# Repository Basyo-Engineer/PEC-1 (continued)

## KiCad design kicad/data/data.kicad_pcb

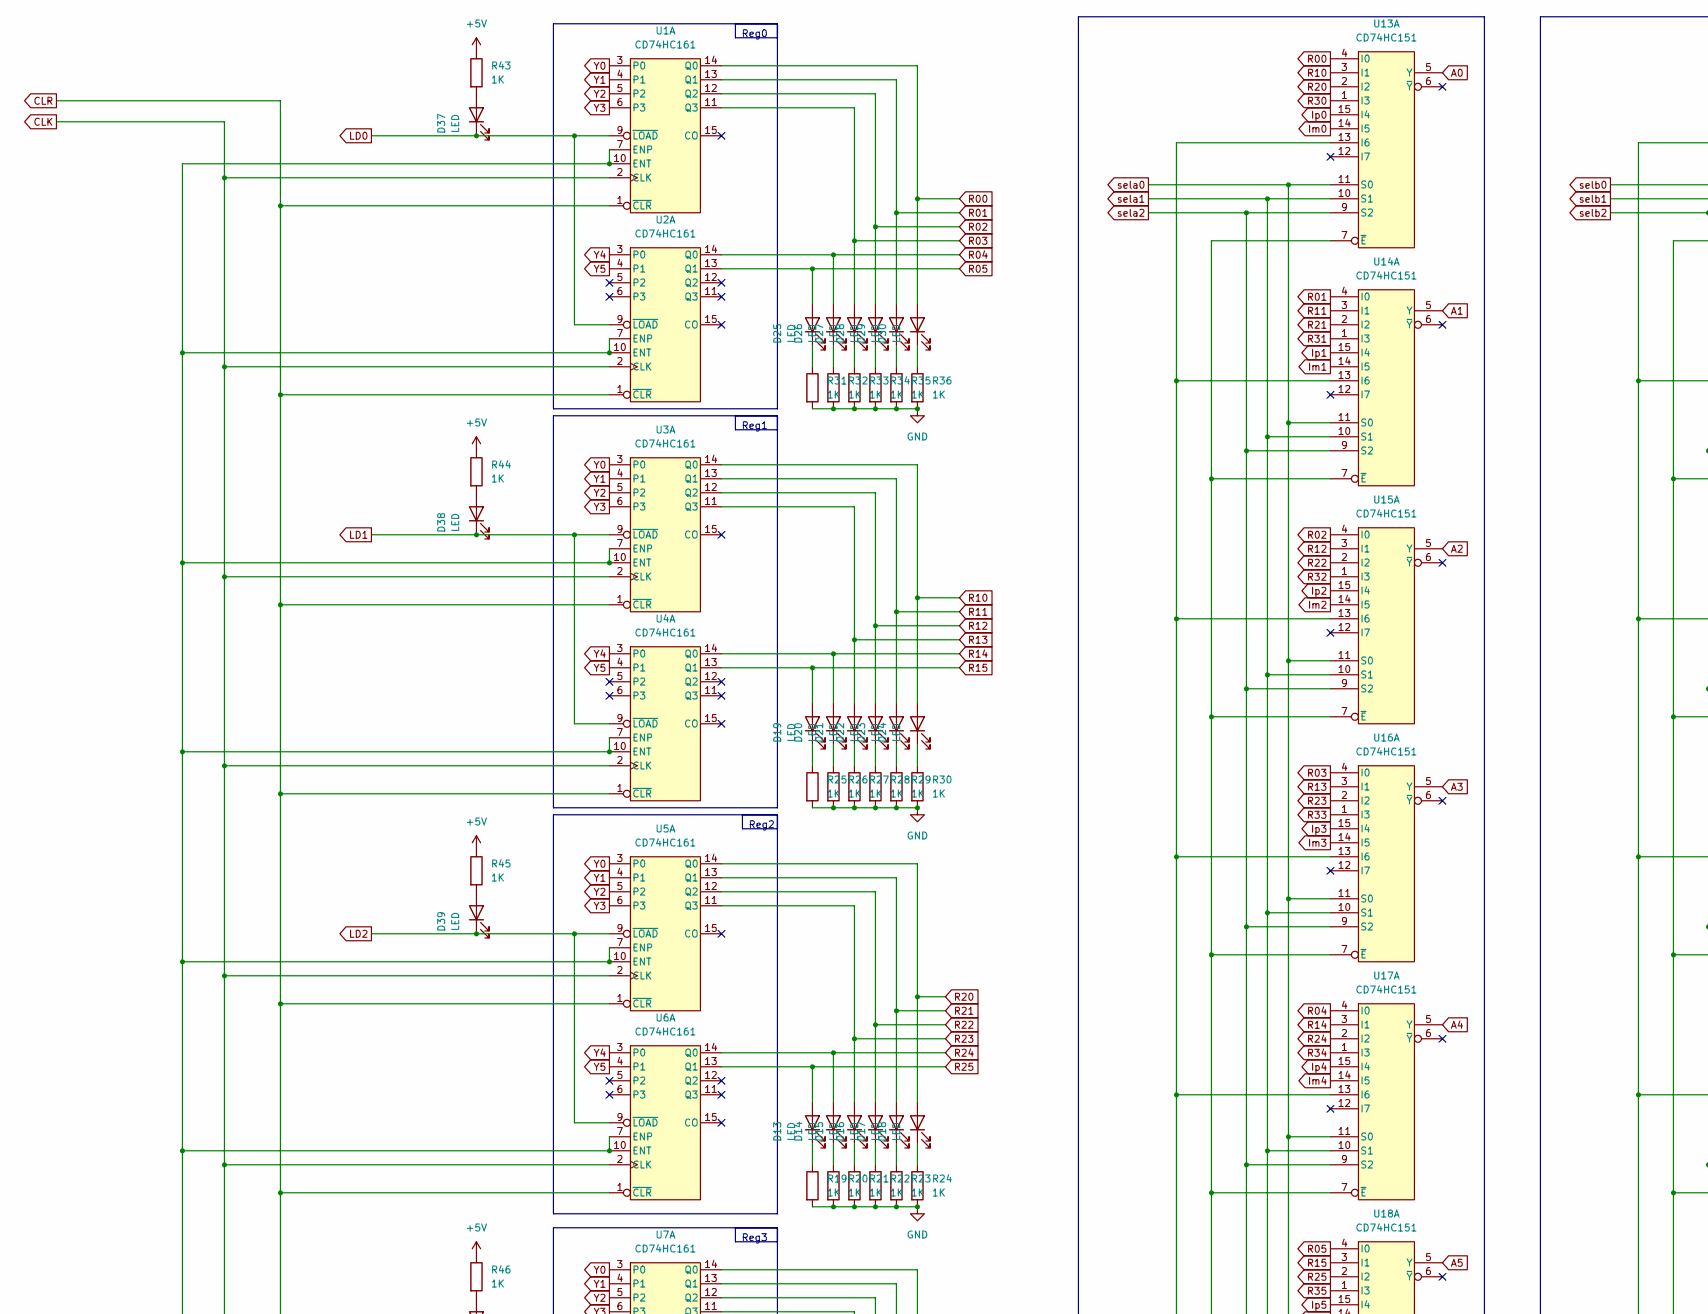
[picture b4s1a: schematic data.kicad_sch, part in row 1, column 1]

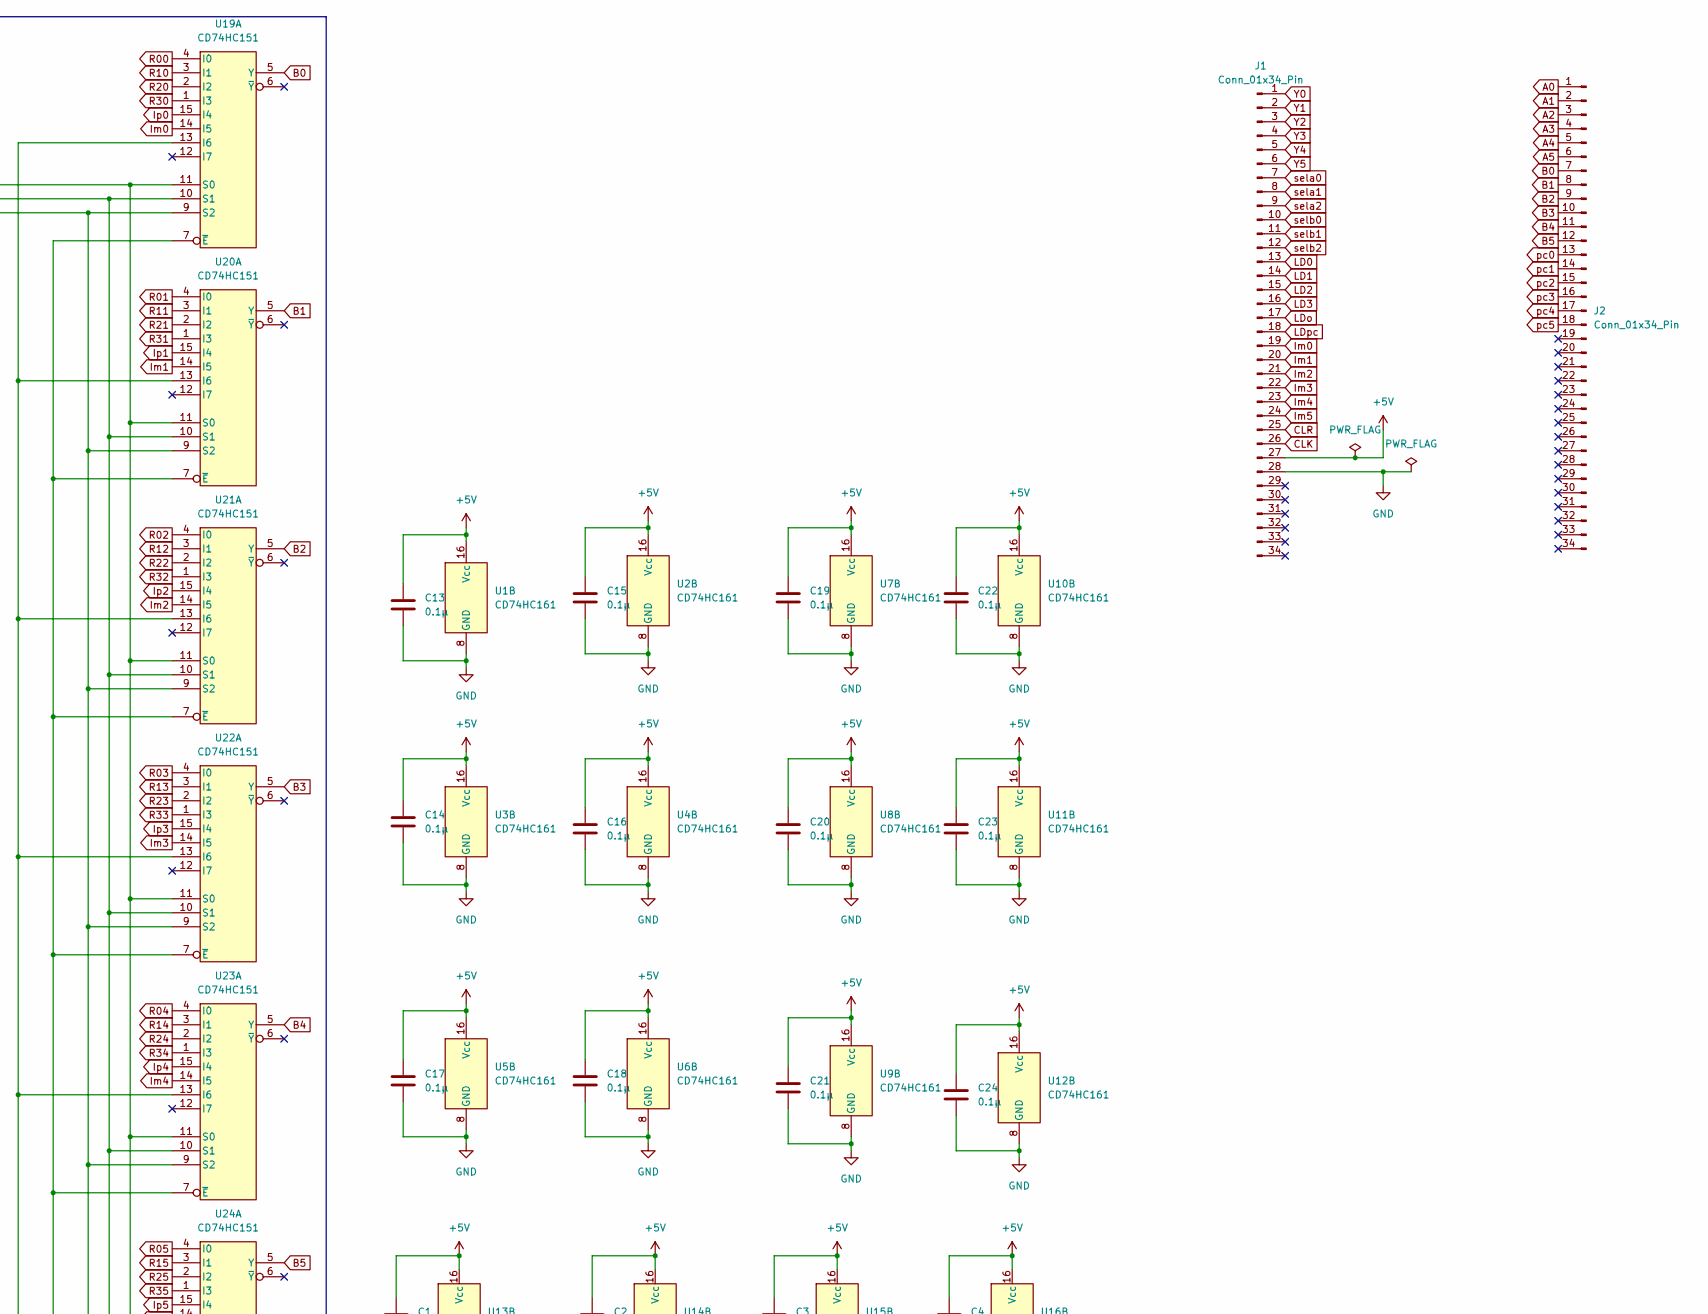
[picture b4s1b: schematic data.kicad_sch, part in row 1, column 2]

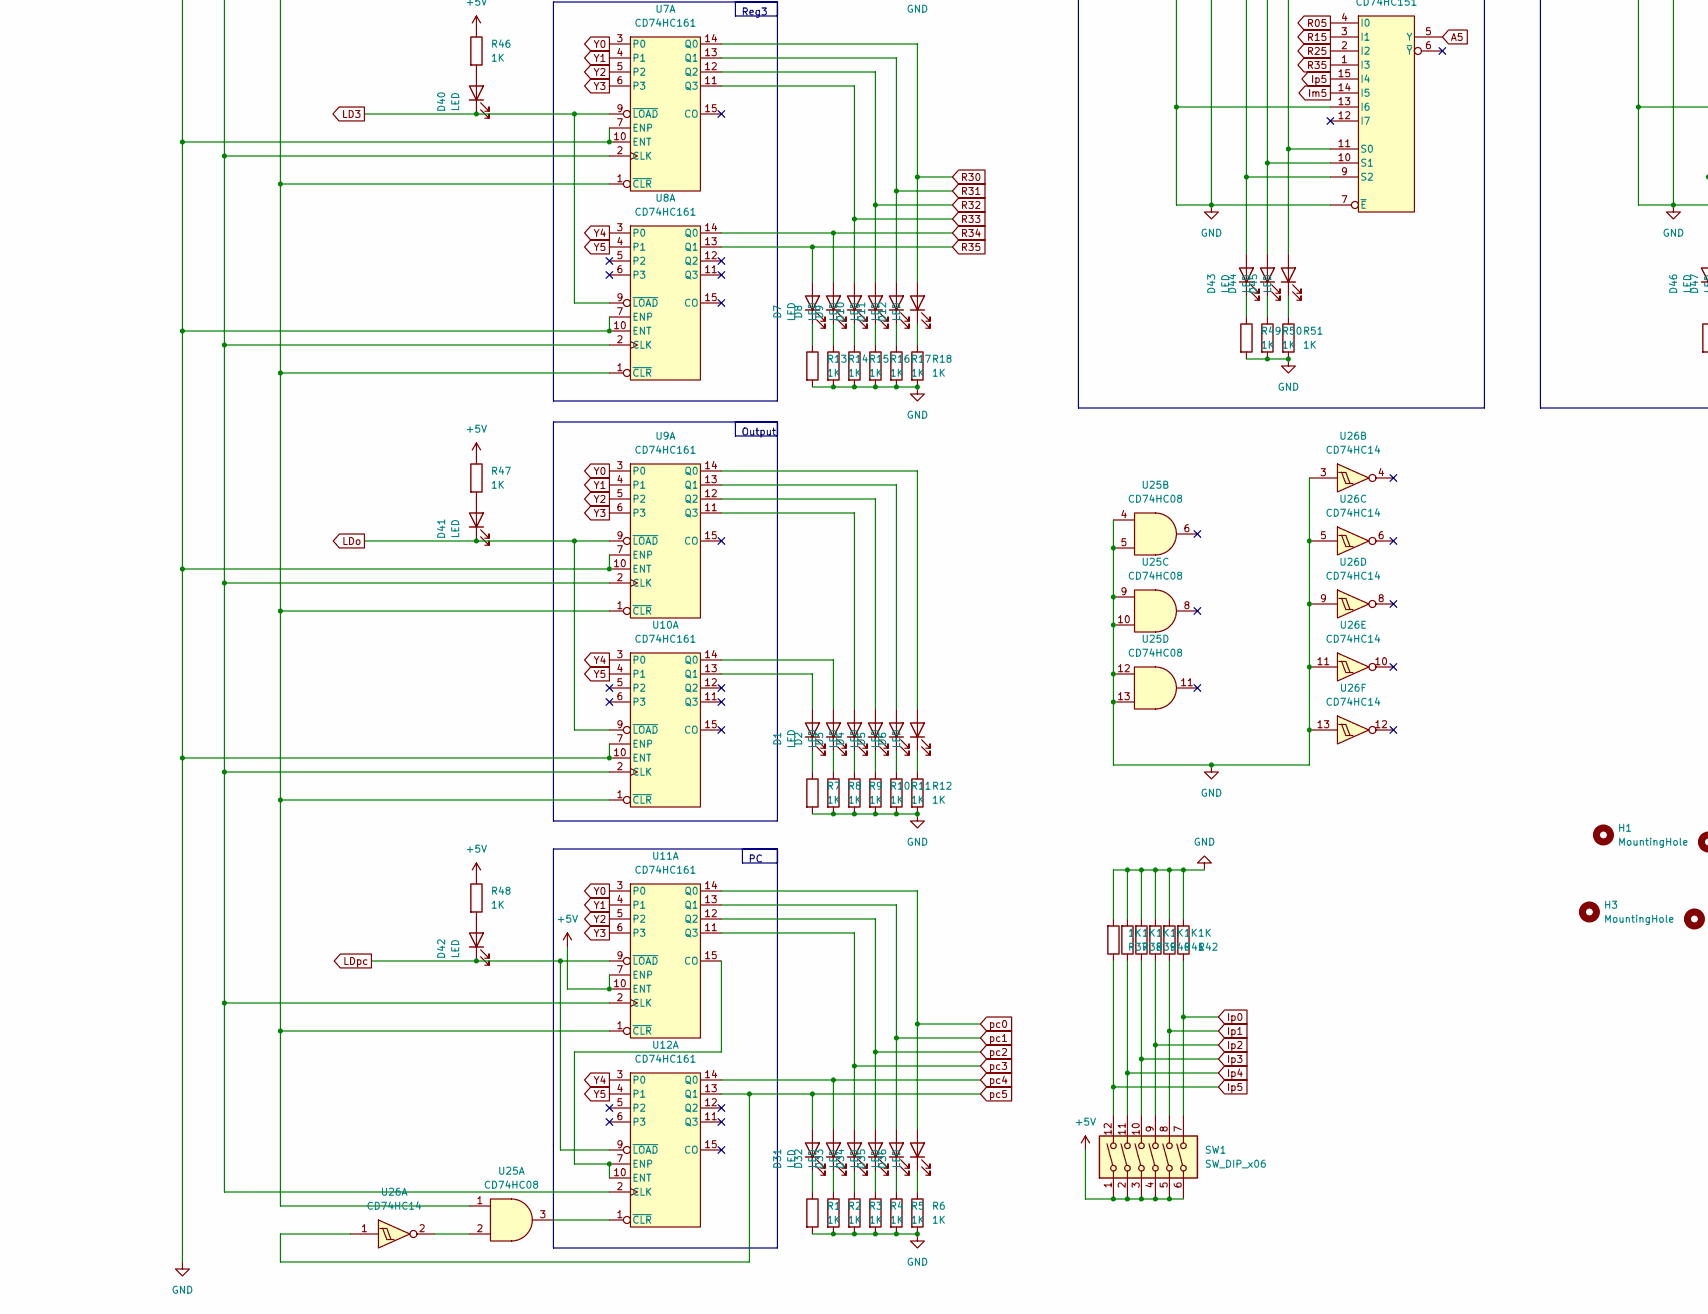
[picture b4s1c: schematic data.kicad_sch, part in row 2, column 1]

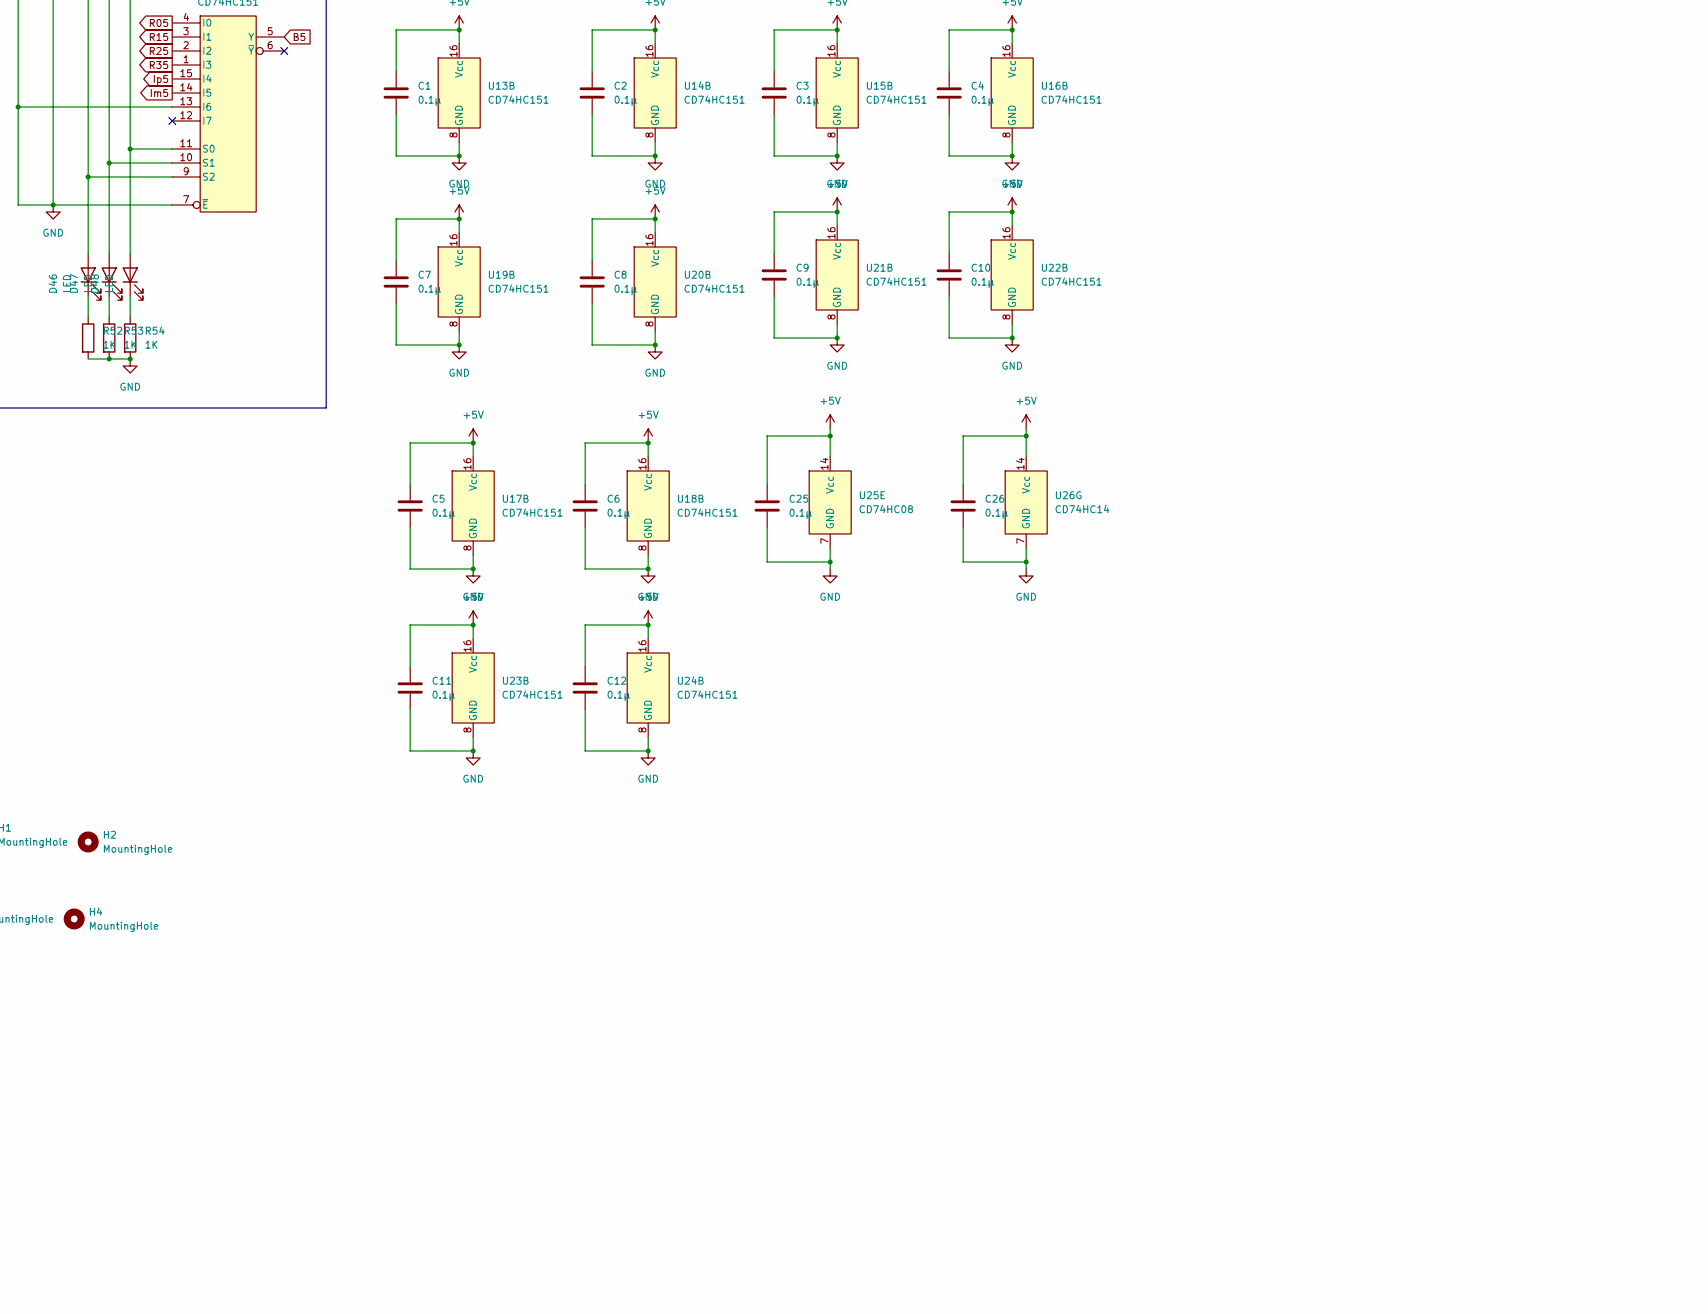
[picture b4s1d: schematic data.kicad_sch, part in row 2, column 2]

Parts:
C1, C2, C3, C4, C5, C6, C7, C8, C9, C10, C11, C12, C13, C14, C15, C16, C17, C18, C19, C20, C21, C22, C23, C24, C25, C26: 0.1μ; C_Disc_D5.0mm_W2.5mm_P2.50mm
D1, D2, D3, D4, D5, D6, D7, D8, D9, D10, D11, D12, D13, D14, D15, D16, D17, D18, D19, D20, D21, D22, D23, D24, D25, D26, D27, D28, D29, D30, D31, D32, D33, D34, D35, D36, D37, D38, D39, D40, D41, D42, D43, D44, D45, D46, D47, D48: LED; LED_D3.0mm
H1, H2, H3, H4: MountingHole; MountingHole_3.2mm_M3
J1, J2: Conn_01x34_Pin; PinHeader_2x17_P2.54mm_Horizontal
R1, R2, R3, R4, R5, R6, R7, R8, R9, R10, R11, R12, R13, R14, R15, R16, R17, R18, R19, R20, R21, R22, R23, R24, R25, R26, R27, R28, R29, R30, R31, R32, R33, R34, R35, R36, R37, R38, R39, R40, R41, R42, R43, R44, R45, R46, R47, R48, R49, R50, R51, R52, R53, R54: 1K; R_Axial_DIN0207_L6.3mm_D2.5mm_P10.16mm_Horizontal
SW1: SW_DIP_x06; DIP-12_W7.62mm_Socket
U1, U2, U3, U4, U5, U6, U7, U8, U9, U10, U11, U12: CD74HC161; DIP-16_W7.62mm_Socket
U13, U14, U15, U16, U17, U18, U19, U20, U21, U22, U23, U24: CD74HC151; DIP-16_W7.62mm_Socket
U25: CD74HC08; DIP-14_W7.62mm_Socket
U26: CD74HC14; DIP-14_W7.62mm_Socket

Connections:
+5V: C1.1, C2.1, C3.1, C4.1, C5.1, C6.1, C7.1, C8.1, C9.1, C10.1, C11.1, C12.1, C13.1, C14.1, C15.1, C16.1, C17.1, C18.1, C19.1, C20.1, C21.1, C22.1, C23.1, C24.1, C25.1, C26.1, J1.27, R43.1, R44.1, R45.1, R46.1, R47.1, R48.1, SW1.1, SW1.2, SW1.3, SW1.4, SW1.5, SW1.6, U1.16 (Vcc), U2.16 (Vcc), U3.16 (Vcc), U4.16 (Vcc), U5.16 (Vcc), U6.16 (Vcc), U7.16 (Vcc), U8.16 (Vcc), U9.16 (Vcc), U10.16 (Vcc), U11.7 (ENP), U11.10 (ENT), U11.16 (Vcc), U12.16 (Vcc), U13.16 (Vcc), U14.16 (Vcc), U15.16 (Vcc), U16.16 (Vcc), U17.16 (Vcc), U18.16 (Vcc), U19.16 (Vcc), U20.16 (Vcc), U21.16 (Vcc), U22.16 (Vcc), U23.16 (Vcc), U24.16 (Vcc), U25.14 (Vcc), U26.14 (Vcc)
A0: J2.1, U13.5 (Y)
A1: J2.2, U14.5 (Y)
A2: J2.3, U15.5 (Y)
A3: J2.4, U16.5 (Y)
A4: J2.5, U17.5 (Y)
A5: J2.6, U18.5 (Y)
B0: J2.7, U19.5 (Y)
B1: J2.8, U20.5 (Y)
B2: J2.9, U21.5 (Y)
B3: J2.10, U22.5 (Y)
B4: J2.11, U23.5 (Y)
B5: J2.12, U24.5 (Y)
CLK: J1.26, U1.2 (CLK), U2.2 (CLK), U3.2 (CLK), U4.2 (CLK), U5.2 (CLK), U6.2 (CLK), U7.2 (CLK), U8.2 (CLK), U9.2 (CLK), U10.2 (CLK), U11.2 (CLK), U12.2 (CLK)
CLR: J1.25, U1.1 (~CLR), U2.1 (~CLR), U3.1 (~CLR), U4.1 (~CLR), U5.1 (~CLR), U6.1 (~CLR), U7.1 (~CLR), U8.1 (~CLR), U9.1 (~CLR), U10.1 (~CLR), U11.1 (~CLR), U25.1
GND: C1.2, C2.2, C3.2, C4.2, C5.2, C6.2, C7.2, C8.2, C9.2, C10.2, C11.2, C12.2, C13.2, C14.2, C15.2, C16.2, C17.2, C18.2, C19.2, C20.2, C21.2, C22.2, C23.2, C24.2, C25.2, C26.2, J1.28, R1.2, R2.2, R3.2, R4.2, R5.2, R6.2, R7.2, R8.2, R9.2, R10.2, R11.2, R12.2, R13.2, R14.2, R15.2, R16.2, R17.2, R18.2, R19.2, R20.2, R21.2, R22.2, R23.2, R24.2, R25.2, R26.2, R27.2, R28.2, R29.2, R30.2, R31.2, R32.2, R33.2, R34.2, R35.2, R36.2, R37.2, R38.2, R39.2, R40.2, R41.2, R42.2, R49.2, R50.2, R51.2, R52.2, R53.2, R54.2, U1.7 (ENP), U1.8 (GND), U1.10 (ENT), U2.7 (ENP), U2.8 (GND), U2.10 (ENT), U3.7 (ENP), U3.8 (GND), U3.10 (ENT), U4.7 (ENP), U4.8 (GND), U4.10 (ENT), U5.7 (ENP), U5.8 (GND), U5.10 (ENT), U6.7 (ENP), U6.8 (GND), U6.10 (ENT), U7.7 (ENP), U7.8 (GND), U7.10 (ENT), U8.7 (ENP), U8.8 (GND), U8.10 (ENT), U9.7 (ENP), U9.8 (GND), U9.10 (ENT), U10.7 (ENP), U10.8 (GND), U10.10 (ENT), U11.8 (GND), U12.8 (GND), U13.7 (~E), U13.8 (GND), U13.13 (I6), U14.7 (~E), U14.8 (GND), U14.13 (I6), U15.7 (~E), U15.8 (GND), U15.13 (I6), U16.7 (~E), U16.8 (GND), U16.13 (I6), U17.7 (~E), U17.8 (GND), U17.13 (I6), U18.7 (~E), U18.8 (GND), U18.13 (I6), U19.7 (~E), U19.8 (GND), U19.13 (I6), U20.7 (~E), U20.8 (GND), U20.13 (I6), U21.7 (~E), U21.8 (GND), U21.13 (I6), U22.7 (~E), U22.8 (GND), U22.13 (I6), U23.7 (~E), U23.8 (GND), U23.13 (I6), U24.7 (~E), U24.8 (GND), U24.13 (I6), U25.4, U25.5, U25.7 (GND), U25.9, U25.10, U25.12, U25.13, U26.3, U26.5, U26.7 (GND), U26.9, U26.11, U26.13
Im0: J1.19, U13.14 (I5), U19.14 (I5)
Im1: J1.20, U14.14 (I5), U20.14 (I5)
Im2: J1.21, U15.14 (I5), U21.14 (I5)
Im3: J1.22, U16.14 (I5), U22.14 (I5)
Im4: J1.23, U17.14 (I5), U23.14 (I5)
Im5: J1.24, U18.14 (I5), U24.14 (I5)
Ip0: R42.1, SW1.7, U13.15 (I4), U19.15 (I4)
Ip1: R41.1, SW1.8, U14.15 (I4), U20.15 (I4)
Ip2: R40.1, SW1.9, U15.15 (I4), U21.15 (I4)
Ip3: R39.1, SW1.10, U16.15 (I4), U22.15 (I4)
Ip4: R38.1, SW1.11, U17.15 (I4), U23.15 (I4)
Ip5: R37.1, SW1.12, U18.15 (I4), U24.15 (I4)
LD0: D37.1 (K), J1.13, U1.9 (~LOAD), U2.9 (~LOAD)
LD1: D38.1 (K), J1.14, U3.9 (~LOAD), U4.9 (~LOAD)
LD2: D39.1 (K), J1.15, U5.9 (~LOAD), U6.9 (~LOAD)
LD3: D40.1 (K), J1.16, U7.9 (~LOAD), U8.9 (~LOAD)
LDo: D41.1 (K), J1.17, U9.9 (~LOAD), U10.9 (~LOAD)
LDpc: D42.1 (K), J1.18, U11.9 (~LOAD), U12.9 (~LOAD)
unnamed: D1.2 (A), U10.13 (Q1)
unnamed: D1.1 (K), R7.1
unnamed: D2.2 (A), U10.14 (Q0)
unnamed: D2.1 (K), R8.1
unnamed: D3.2 (A), U9.11 (Q3)
unnamed: D3.1 (K), R9.1
unnamed: D4.2 (A), U9.12 (Q2)
unnamed: D4.1 (K), R10.1
unnamed: D5.2 (A), U9.13 (Q1)
unnamed: D5.1 (K), R11.1
unnamed: D6.2 (A), U9.14 (Q0)
unnamed: D6.1 (K), R12.1
unnamed: D7.1 (K), R13.1
unnamed: D8.1 (K), R14.1
unnamed: D9.1 (K), R15.1
unnamed: D10.1 (K), R16.1
unnamed: D11.1 (K), R17.1
unnamed: D12.1 (K), R18.1
unnamed: D13.1 (K), R19.1
unnamed: D14.1 (K), R20.1
unnamed: D15.1 (K), R21.1
unnamed: D16.1 (K), R22.1
unnamed: D17.1 (K), R23.1
unnamed: D18.1 (K), R24.1
unnamed: D19.1 (K), R25.1
unnamed: D20.1 (K), R26.1
unnamed: D21.1 (K), R27.1
unnamed: D22.1 (K), R28.1
unnamed: D23.1 (K), R29.1
unnamed: D24.1 (K), R30.1
unnamed: D25.1 (K), R31.1
unnamed: D26.1 (K), R32.1
unnamed: D27.1 (K), R33.1
unnamed: D28.1 (K), R34.1
unnamed: D29.1 (K), R35.1
unnamed: D30.1 (K), R36.1
unnamed: D31.1 (K), R1.1
unnamed: D32.1 (K), R2.1
unnamed: D33.1 (K), R3.1
unnamed: D34.1 (K), R4.1
unnamed: D35.1 (K), R5.1
unnamed: D36.1 (K), R6.1
unnamed: D37.2 (A), R43.2
unnamed: D38.2 (A), R44.2
unnamed: D39.2 (A), R45.2
unnamed: D40.2 (A), R46.2
unnamed: D41.2 (A), R47.2
unnamed: D42.2 (A), R48.2
unnamed: D43.1 (K), R49.1
unnamed: D44.1 (K), R50.1
unnamed: D45.1 (K), R51.1
unnamed: D46.1 (K), R52.1
unnamed: D47.1 (K), R53.1
unnamed: D48.1 (K), R54.1
unnamed: U11.15 (CO), U12.7 (ENP), U12.10 (ENT)
unnamed: U12.1 (~CLR), U25.3
unnamed: U25.2, U26.2
R00: D30.2 (A), U1.14 (Q0), U13.4 (I0), U19.4 (I0)
R01: D29.2 (A), U1.13 (Q1), U14.4 (I0), U20.4 (I0)
R02: D28.2 (A), U1.12 (Q2), U15.4 (I0), U21.4 (I0)
R03: D27.2 (A), U1.11 (Q3), U16.4 (I0), U22.4 (I0)
R04: D26.2 (A), U2.14 (Q0), U17.4 (I0), U23.4 (I0)
R05: D25.2 (A), U2.13 (Q1), U18.4 (I0), U24.4 (I0)
R10: D24.2 (A), U3.14 (Q0), U13.3 (I1), U19.3 (I1)
R11: D23.2 (A), U3.13 (Q1), U14.3 (I1), U20.3 (I1)
R12: D22.2 (A), U3.12 (Q2), U15.3 (I1), U21.3 (I1)
R13: D21.2 (A), U3.11 (Q3), U16.3 (I1), U22.3 (I1)
R14: D20.2 (A), U4.14 (Q0), U17.3 (I1), U23.3 (I1)
R15: D19.2 (A), U4.13 (Q1), U18.3 (I1), U24.3 (I1)
R20: D18.2 (A), U5.14 (Q0), U13.2 (I2), U19.2 (I2)
R21: D17.2 (A), U5.13 (Q1), U14.2 (I2), U20.2 (I2)
R22: D16.2 (A), U5.12 (Q2), U15.2 (I2), U21.2 (I2)
R23: D15.2 (A), U5.11 (Q3), U16.2 (I2), U22.2 (I2)
R24: D14.2 (A), U6.14 (Q0), U17.2 (I2), U23.2 (I2)
R25: D13.2 (A), U6.13 (Q1), U18.2 (I2), U24.2 (I2)
R30: D12.2 (A), U7.14 (Q0), U13.1 (I3), U19.1 (I3)
R31: D11.2 (A), U7.13 (Q1), U14.1 (I3), U20.1 (I3)
R32: D10.2 (A), U7.12 (Q2), U15.1 (I3), U21.1 (I3)
R33: D9.2 (A), U7.11 (Q3), U16.1 (I3), U22.1 (I3)
R34: D8.2 (A), U8.14 (Q0), U17.1 (I3), U23.1 (I3)
R35: D7.2 (A), U8.13 (Q1), U18.1 (I3), U24.1 (I3)
Y0: J1.1, U1.3 (P0), U3.3 (P0), U5.3 (P0), U7.3 (P0), U9.3 (P0), U11.3 (P0)
Y1: J1.2, U1.4 (P1), U3.4 (P1), U5.4 (P1), U7.4 (P1), U9.4 (P1), U11.4 (P1)
Y2: J1.3, U1.5 (P2), U3.5 (P2), U5.5 (P2), U7.5 (P2), U9.5 (P2), U11.5 (P2)
Y3: J1.4, U1.6 (P3), U3.6 (P3), U5.6 (P3), U7.6 (P3), U9.6 (P3), U11.6 (P3)
Y4: J1.5, U2.3 (P0), U4.3 (P0), U6.3 (P0), U8.3 (P0), U10.3 (P0), U12.3 (P0)
Y5: J1.6, U2.4 (P1), U4.4 (P1), U6.4 (P1), U8.4 (P1), U10.4 (P1), U12.4 (P1)
pc0: D36.2 (A), J2.13, U11.14 (Q0)
pc1: D35.2 (A), J2.14, U11.13 (Q1)
pc2: D34.2 (A), J2.15, U11.12 (Q2)
pc3: D33.2 (A), J2.16, U11.11 (Q3)
pc4: D32.2 (A), J2.17, U12.14 (Q0)
pc5: D31.2 (A), J2.18, U12.13 (Q1), U26.1
sela0: D45.2 (A), J1.7, U13.11 (S0), U14.11 (S0), U15.11 (S0), U16.11 (S0), U17.11 (S0), U18.11 (S0)
sela1: D44.2 (A), J1.8, U13.10 (S1), U14.10 (S1), U15.10 (S1), U16.10 (S1), U17.10 (S1), U18.10 (S1)
sela2: D43.2 (A), J1.9, U13.9 (S2), U14.9 (S2), U15.9 (S2), U16.9 (S2), U17.9 (S2), U18.9 (S2)
selb0: D48.2 (A), J1.10, U19.11 (S0), U20.11 (S0), U21.11 (S0), U22.11 (S0), U23.11 (S0), U24.11 (S0)
selb1: D47.2 (A), J1.11, U19.10 (S1), U20.10 (S1), U21.10 (S1), U22.10 (S1), U23.10 (S1), U24.10 (S1)
selb2: D46.2 (A), J1.12, U19.9 (S2), U20.9 (S2), U21.9 (S2), U22.9 (S2), U23.9 (S2), U24.9 (S2)

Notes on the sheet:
Reg3
Reg0
Reg1
Output
Reg2

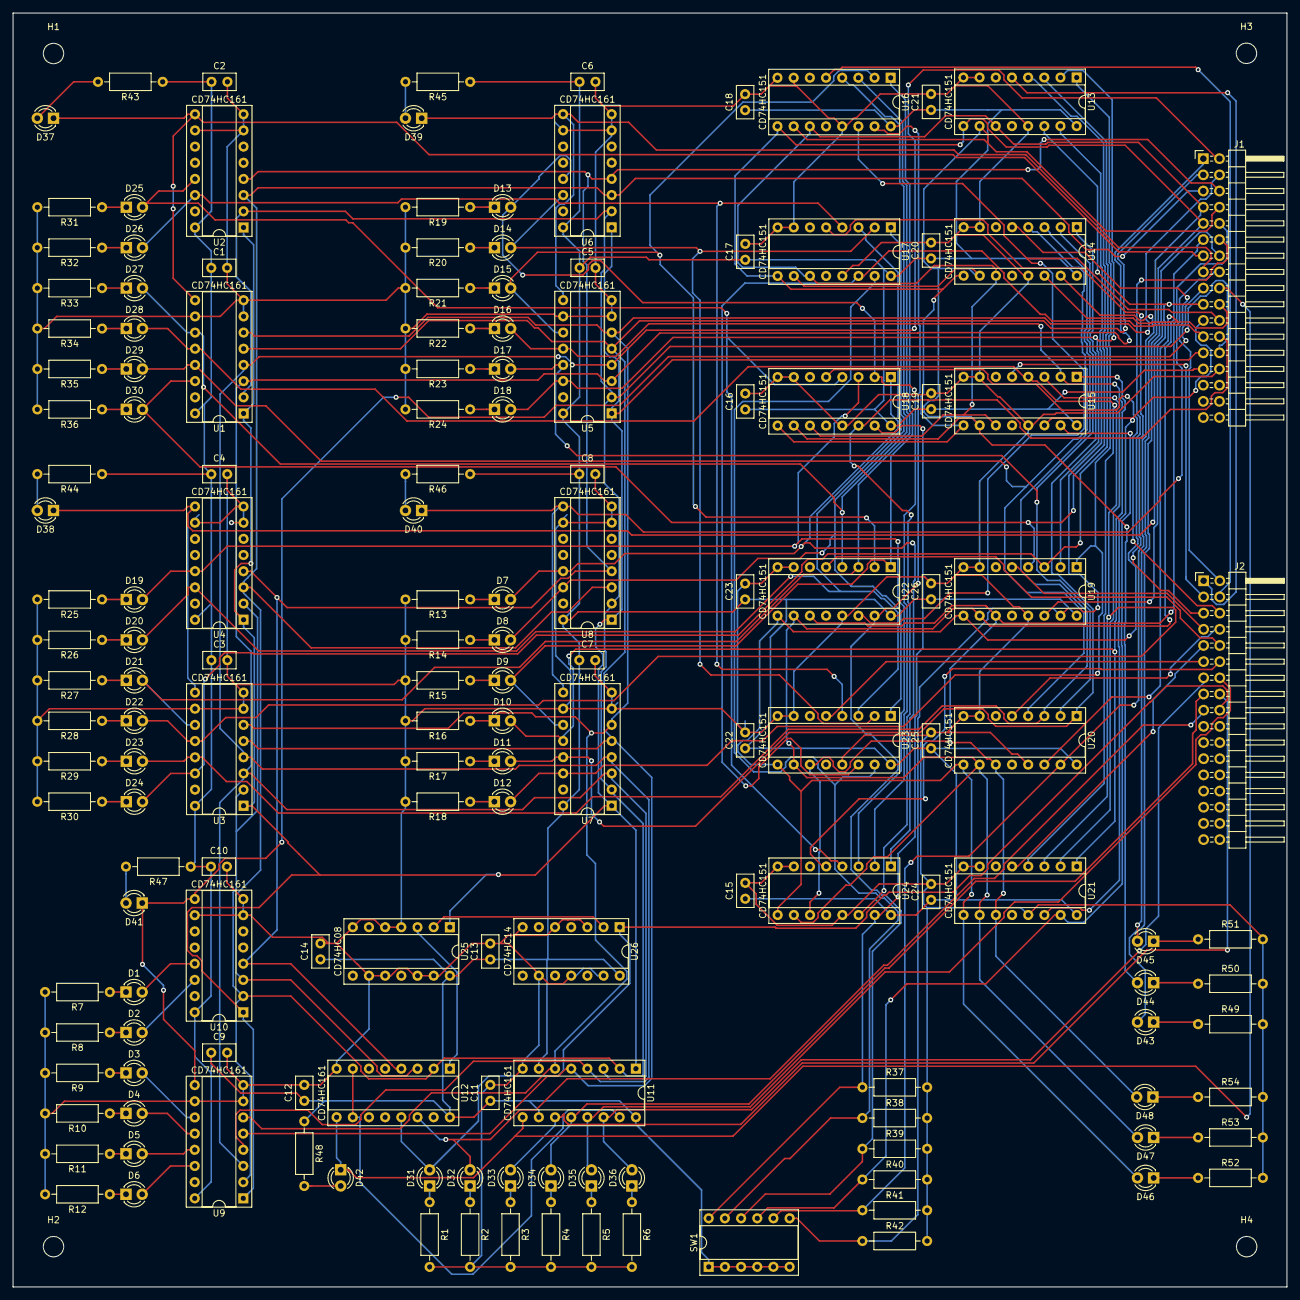
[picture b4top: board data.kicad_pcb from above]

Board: 2 copper layers, 200.0 x 200.0 mm, 161 parts (0 on the bottom side), 133 nets.
